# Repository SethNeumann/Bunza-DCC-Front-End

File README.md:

# REPO NAME: Bunza-DCC-Front-End

## License: Creative Commons Attribution-NonCommercial-ShareAlike

Design based on Geoff Bunza's SMA-37 blog post about an updated DCC Front end

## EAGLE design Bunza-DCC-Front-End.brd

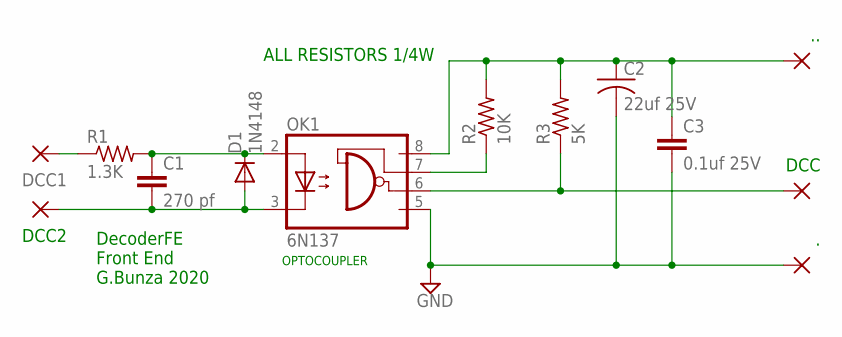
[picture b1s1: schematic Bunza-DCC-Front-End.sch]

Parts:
., ..: 2,15/1,0
C1: 270 pf; AXIAL-5MM
C2: 22uf 25V; C050-035X075
C3: 0.1uf 25V; AXIAL-5MM
D1: 1N4148; DO35-7
DCC, DCC1, DCC2: 2,15/1,0
OK1: 6N137; DIL08
R1: 1.3K; 0204/7
R2: 10K; 0204/7
R3: 5K; 0204/7

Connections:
GND: ..1, C2.2, C3.P$2 (2), OK1.5 (GND)
unnamed: DCC1.1, R1.1
unnamed: DCC.1, OK1.6 (VO), R3.1
unnamed: OK1.7 (VE), R2.1
unnamed: ...1, C2.1, C3.P$1 (1), OK1.8 (VCC), R2.2, R3.2
unnamed: C1.P$1 (1), D1.C, OK1.2 (A), R1.2
unnamed: C1.P$2 (2), D1.A, DCC2.1, OK1.3 (C)

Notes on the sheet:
OPTOCOUPLER
ALL RESISTORS 1/4W
DecoderFE Front End G.Bunza 2020

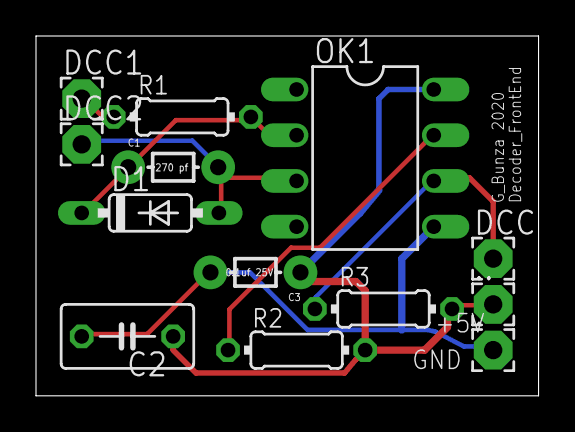
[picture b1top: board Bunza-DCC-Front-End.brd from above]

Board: 2 copper layers, 27.9 x 20.0 mm, 13 parts (0 on the bottom side), 7 nets.

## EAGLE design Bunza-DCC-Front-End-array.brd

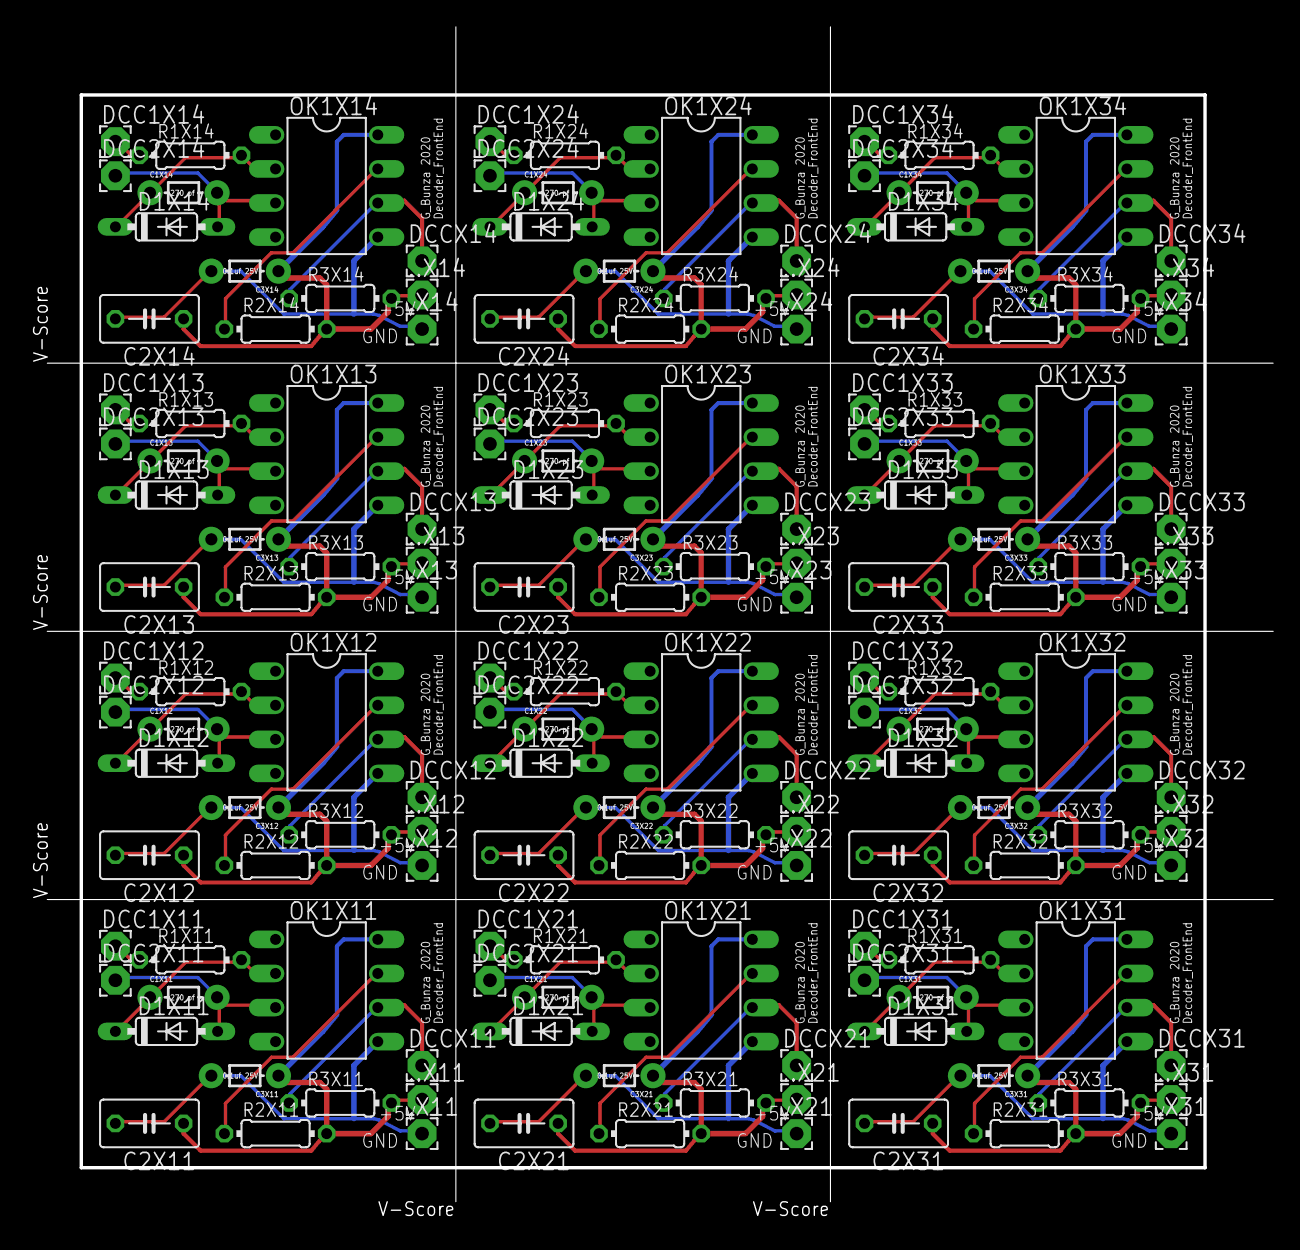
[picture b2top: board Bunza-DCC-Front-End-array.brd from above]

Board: 2 copper layers, 92.6 x 89.0 mm, 156 parts (0 on the bottom side), 84 nets.

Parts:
..X11, ..X12, ..X13, ..X14, ..X21, ..X22, ..X23, ..X24, ..X31, ..X32, ..X33, ..X34, .X11, .X12, .X13, .X14, .X21, .X22, .X23, .X24, .X31, .X32, .X33, .X34: 2,15/1,0
C1X11, C1X12, C1X13, C1X14, C1X21, C1X22, C1X23, C1X24, C1X31, C1X32, C1X33, C1X34: 270 pf; AXIAL-5MM
C2X11, C2X12, C2X13, C2X14, C2X21, C2X22, C2X23, C2X24, C2X31, C2X32, C2X33, C2X34: 22uf 25V; C050-035X075
C3X11, C3X12, C3X13, C3X14, C3X21, C3X22, C3X23, C3X24, C3X31, C3X32, C3X33, C3X34: 0.1uf 25V; AXIAL-5MM
D1X11, D1X12, D1X13, D1X14, D1X21, D1X22, D1X23, D1X24, D1X31, D1X32, D1X33, D1X34: 1N4148; DO35-7
DCC1X11, DCC1X12, DCC1X13, DCC1X14, DCC1X21, DCC1X22, DCC1X23, DCC1X24, DCC1X31, DCC1X32, DCC1X33, DCC1X34, DCC2X11, DCC2X12, DCC2X13, DCC2X14, DCC2X21, DCC2X22, DCC2X23, DCC2X24, DCC2X31, DCC2X32, DCC2X33, DCC2X34: 2,15/1,0
DCCX11, DCCX12, DCCX13, DCCX14, DCCX21, DCCX22, DCCX23, DCCX24, DCCX31, DCCX32, DCCX33, DCCX34: 2,15/1,0
OK1X11, OK1X12, OK1X13, OK1X14, OK1X21, OK1X22, OK1X23, OK1X24, OK1X31, OK1X32, OK1X33, OK1X34: 6N137; DIL08
R1X11, R1X12, R1X13, R1X14, R1X21, R1X22, R1X23, R1X24, R1X31, R1X32, R1X33, R1X34: 1.3K; 0204/7
R2X11, R2X12, R2X13, R2X14, R2X21, R2X22, R2X23, R2X24, R2X31, R2X32, R2X33, R2X34: 10K; 0204/7
R3X11, R3X12, R3X13, R3X14, R3X21, R3X22, R3X23, R3X24, R3X31, R3X32, R3X33, R3X34: 5K; 0204/7

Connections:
GNDX11: .X11.1, C2X11.2, C3X11.P$2, OK1X11.5
GNDX12: .X12.1, C2X12.2, C3X12.P$2, OK1X12.5
GNDX13: .X13.1, C2X13.2, C3X13.P$2, OK1X13.5
GNDX14: .X14.1, C2X14.2, C3X14.P$2, OK1X14.5
GNDX21: .X21.1, C2X21.2, C3X21.P$2, OK1X21.5
GNDX22: .X22.1, C2X22.2, C3X22.P$2, OK1X22.5
GNDX23: .X23.1, C2X23.2, C3X23.P$2, OK1X23.5
GNDX24: .X24.1, C2X24.2, C3X24.P$2, OK1X24.5
GNDX31: .X31.1, C2X31.2, C3X31.P$2, OK1X31.5
GNDX32: .X32.1, C2X32.2, C3X32.P$2, OK1X32.5
GNDX33: .X33.1, C2X33.2, C3X33.P$2, OK1X33.5
GNDX34: .X34.1, C2X34.2, C3X34.P$2, OK1X34.5
unnamed: DCC1X11.1, R1X11.1
unnamed: DCC1X12.1, R1X12.1
unnamed: DCC1X13.1, R1X13.1
unnamed: DCC1X14.1, R1X14.1
unnamed: DCC1X21.1, R1X21.1
unnamed: DCC1X22.1, R1X22.1
unnamed: DCC1X23.1, R1X23.1
unnamed: DCC1X24.1, R1X24.1
unnamed: DCC1X31.1, R1X31.1
unnamed: DCC1X32.1, R1X32.1
unnamed: DCC1X33.1, R1X33.1
unnamed: DCC1X34.1, R1X34.1
unnamed: DCCX11.1, OK1X11.6, R3X11.1
unnamed: DCCX12.1, OK1X12.6, R3X12.1
unnamed: DCCX13.1, OK1X13.6, R3X13.1
unnamed: DCCX14.1, OK1X14.6, R3X14.1
unnamed: DCCX21.1, OK1X21.6, R3X21.1
unnamed: DCCX22.1, OK1X22.6, R3X22.1
unnamed: DCCX23.1, OK1X23.6, R3X23.1
unnamed: DCCX24.1, OK1X24.6, R3X24.1
unnamed: DCCX31.1, OK1X31.6, R3X31.1
unnamed: DCCX32.1, OK1X32.6, R3X32.1
unnamed: DCCX33.1, OK1X33.6, R3X33.1
unnamed: DCCX34.1, OK1X34.6, R3X34.1
unnamed: OK1X11.7, R2X11.1
unnamed: OK1X12.7, R2X12.1
unnamed: OK1X13.7, R2X13.1
unnamed: OK1X14.7, R2X14.1
unnamed: OK1X21.7, R2X21.1
unnamed: OK1X22.7, R2X22.1
unnamed: OK1X23.7, R2X23.1
unnamed: OK1X24.7, R2X24.1
unnamed: OK1X31.7, R2X31.1
unnamed: OK1X32.7, R2X32.1
unnamed: OK1X33.7, R2X33.1
unnamed: OK1X34.7, R2X34.1
unnamed: ..X11.1, C2X11.1, C3X11.P$1, OK1X11.8, R2X11.2, R3X11.2
unnamed: ..X12.1, C2X12.1, C3X12.P$1, OK1X12.8, R2X12.2, R3X12.2
unnamed: ..X13.1, C2X13.1, C3X13.P$1, OK1X13.8, R2X13.2, R3X13.2
unnamed: ..X14.1, C2X14.1, C3X14.P$1, OK1X14.8, R2X14.2, R3X14.2
unnamed: ..X21.1, C2X21.1, C3X21.P$1, OK1X21.8, R2X21.2, R3X21.2
unnamed: ..X22.1, C2X22.1, C3X22.P$1, OK1X22.8, R2X22.2, R3X22.2
unnamed: ..X23.1, C2X23.1, C3X23.P$1, OK1X23.8, R2X23.2, R3X23.2
unnamed: ..X24.1, C2X24.1, C3X24.P$1, OK1X24.8, R2X24.2, R3X24.2
unnamed: ..X31.1, C2X31.1, C3X31.P$1, OK1X31.8, R2X31.2, R3X31.2
unnamed: ..X32.1, C2X32.1, C3X32.P$1, OK1X32.8, R2X32.2, R3X32.2
unnamed: ..X33.1, C2X33.1, C3X33.P$1, OK1X33.8, R2X33.2, R3X33.2
unnamed: ..X34.1, C2X34.1, C3X34.P$1, OK1X34.8, R2X34.2, R3X34.2
unnamed: C1X11.P$1, D1X11.C, OK1X11.2, R1X11.2
unnamed: C1X12.P$1, D1X12.C, OK1X12.2, R1X12.2
unnamed: C1X13.P$1, D1X13.C, OK1X13.2, R1X13.2
unnamed: C1X14.P$1, D1X14.C, OK1X14.2, R1X14.2
unnamed: C1X21.P$1, D1X21.C, OK1X21.2, R1X21.2
unnamed: C1X22.P$1, D1X22.C, OK1X22.2, R1X22.2
unnamed: C1X23.P$1, D1X23.C, OK1X23.2, R1X23.2
unnamed: C1X24.P$1, D1X24.C, OK1X24.2, R1X24.2
unnamed: C1X31.P$1, D1X31.C, OK1X31.2, R1X31.2
unnamed: C1X32.P$1, D1X32.C, OK1X32.2, R1X32.2
unnamed: C1X33.P$1, D1X33.C, OK1X33.2, R1X33.2
unnamed: C1X34.P$1, D1X34.C, OK1X34.2, R1X34.2
unnamed: C1X11.P$2, D1X11.A, DCC2X11.1, OK1X11.3
unnamed: C1X12.P$2, D1X12.A, DCC2X12.1, OK1X12.3
unnamed: C1X13.P$2, D1X13.A, DCC2X13.1, OK1X13.3
unnamed: C1X14.P$2, D1X14.A, DCC2X14.1, OK1X14.3
unnamed: C1X21.P$2, D1X21.A, DCC2X21.1, OK1X21.3
unnamed: C1X22.P$2, D1X22.A, DCC2X22.1, OK1X22.3
unnamed: C1X23.P$2, D1X23.A, DCC2X23.1, OK1X23.3
unnamed: C1X24.P$2, D1X24.A, DCC2X24.1, OK1X24.3
unnamed: C1X31.P$2, D1X31.A, DCC2X31.1, OK1X31.3
unnamed: C1X32.P$2, D1X32.A, DCC2X32.1, OK1X32.3
unnamed: C1X33.P$2, D1X33.A, DCC2X33.1, OK1X33.3
unnamed: C1X34.P$2, D1X34.A, DCC2X34.1, OK1X34.3

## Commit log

2020-12-29 initial commit
    initial commit
2020-12-29 Update INFO
2020-12-29 initial commit
    moved from EAGLE directory
2021-01-02 changes to support panelization
    Made a panelized 12-up board, see the array,zip file

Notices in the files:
parts and their libraries:
SparkFun-Capacitors: Licensing: CC v3.0 Share-Alike You are welcome to use this library for commercial purposes.
